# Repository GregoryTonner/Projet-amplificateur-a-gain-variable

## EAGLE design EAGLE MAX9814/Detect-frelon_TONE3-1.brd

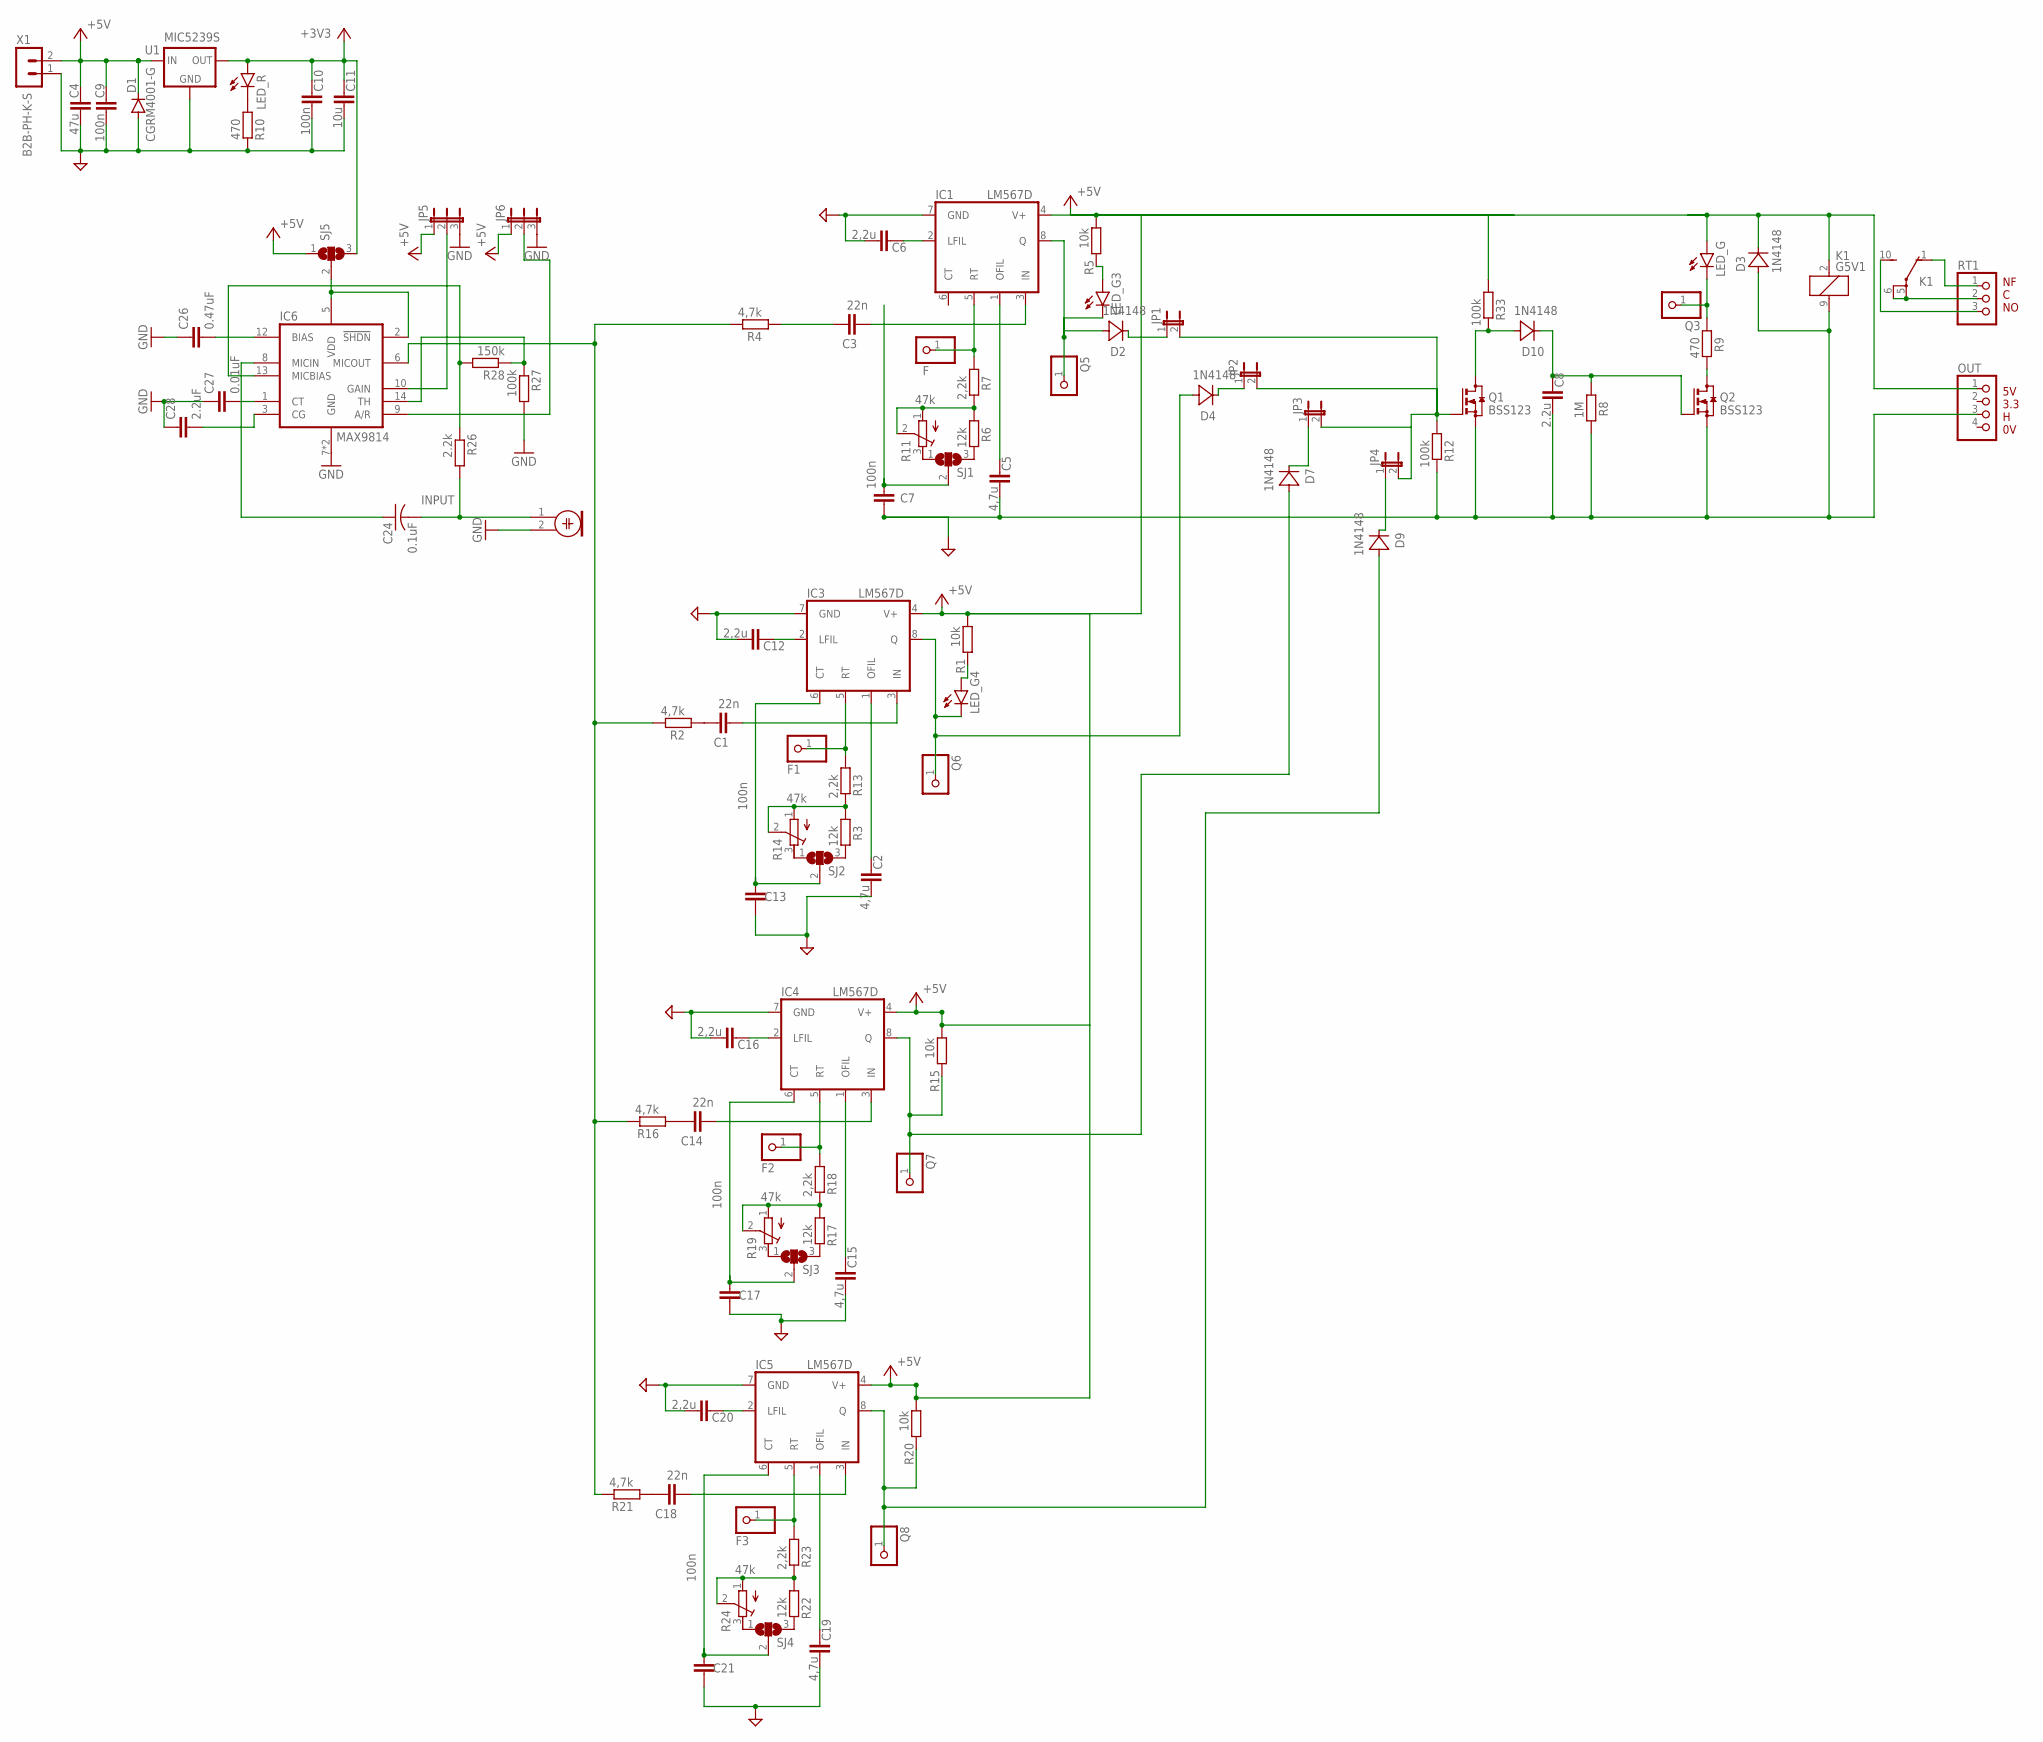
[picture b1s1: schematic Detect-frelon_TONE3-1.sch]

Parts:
C1, C3, C14, C18: 22n; C1206
C2, C5, C15, C19: 4,7u; C1206
C4: 47u; C1210
C6, C12, C16, C20: 2,2u; C1206
C7, C13, C17, C21: 100n; C1210
C8: 2.2u; C1210
C9, C10: 100n; C1206
C11: 10u; C1210
C24: 0.1uF; C0805K
C26: 0.47uF; C1206
C27: 0.01uF; C1206
C28: 2.2uF; C1206
D1: CGRM4001-G; SOD-123_MINI-SMA
D2, D3, D4, D7, D9, D10: 1N4148; VISHAY_1N4148W-E3-08_0
F, F1, F2, F3: PINHD-1X1; 1X01
IC1, IC3, IC4, IC5: LM567D; SO08
IC6: MAX9814; TDFN14-EP
JP1, JP2, JP3, JP4: JP1E; JP1
JP5, JP6: JP2E; JP2
K1: G5V1
LED_G, LED_G3, LED_G4: LEDSMT1206; 1206
LED_R: LEDSMT1206; 1206
M2: ELECTRET_MICROPHON-WM-62PC/62PK; WM-62PC/62PK
OUT: PINHD-1X4; 1X04
Q1, Q2: BSS123; SOT23
Q3, Q5, Q6, Q7, Q8: PINHD-1X1; 1X01
R1, R5, R15, R20: 10k; R1206
R2, R4, R16, R21: 4,7k; R1206
R3, R6, R17, R22: 12k; R1206
R7, R13, R18, R23: 2,2k; R1206
R8: 1M; R1206
R9, R10: 470; R1206
R11, R14, R19, R24: 47k; RTRIM3296W
R12, R27, R33: 100k; R1206
R26: 2.2k; R1206
R28: 150k; R1206
RT1: PINHD-1X3; 1X03
SJ1, SJ2, SJ3, SJ4, SJ5: SJ2W; SJ_2
U1: MIC5239S; SOT223
X1: B2B-PH-K-S

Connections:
+3V3: C10.1, C11.1, LED_R.A, SJ5.3, U1.3 (OUT)
+5V: C4.1, C9.1, D1.C, D3.1 (C), IC1.4 (V+), IC3.4 (V+), IC4.4 (V+), IC5.4 (V+), JP5.1, JP6.1, K1.2 (1), LED_G.A, OUT.1, R1.1, R5.1, R15.1, R20.1, R33.1, SJ5.1, U1.1 (IN), X1.2
GND: C2.2, C4.2, C5.2, C6.2, C7.2, C8.2, C9.2, C10.2, C11.2, C12.2, C13.2, C15.2, C16.2, C17.2, C19.2, C20.2, C21.2, C26.1, C27.1, C28.1, D1.A, D3.2 (A), IC1.7 (GND), IC3.7 (GND), IC4.7 (GND), IC5.7 (GND), IC6.7 (GND), IC6.EP (GND), JP5.3, JP6.3, K1.9 (2), M2.2, OUT.3, Q1.2 (S), Q2.2 (S), R8.2, R10.2, R12.2, R27.2, U1.2 (GND), U1.4 (GND), X1.1
INPUT: C24.2, M2.1, R26.2
unnamed: C3.1, R4.1
unnamed: F.1, IC1.5 (RT), R7.1
unnamed: IC6.10 (GAIN), JP5.2
unnamed: LED_R.C, R10.1
unnamed: C16.1, IC4.2 (LFIL)
unnamed: C8.1, D10.1 (C), Q2.1 (G), R8.1
unnamed: C12.1, IC3.2 (LFIL)
unnamed: C2.1, IC3.1 (OFIL)
unnamed: C6.1, IC1.2 (LFIL)
unnamed: C5.1, IC1.1 (OFIL)
unnamed: R6.2, SJ1.3
unnamed: Q2.3 (D), R9.2
unnamed: R6.1, R7.2, R11.1 (A), R11.2 (S)
unnamed: D2.1 (C), JP1.1
unnamed: LED_G.C, Q3.1, R9.1
unnamed: C1.1, R2.1
unnamed: K1.5, K1.6, RT1.2
unnamed: C13.1, IC3.6 (CT), SJ2.2
unnamed: R11.3 (E), SJ1.1
unnamed: C7.1, SJ1.2
unnamed: LED_G4.A, R1.2
unnamed: F1.1, IC3.5 (RT), R13.1
unnamed: R3.1, R13.2, R14.1 (A), R14.2 (S)
unnamed: C3.2, IC1.3 (IN)
unnamed: D2.2 (A), IC1.8 (Q), LED_G3.C, Q5.1
unnamed: R3.2, SJ2.3
unnamed: R14.3 (E), SJ2.1
unnamed: C1.2, IC3.3 (IN)
unnamed: D4.2 (A), IC3.8 (Q), LED_G4.C, Q6.1
unnamed: C15.1, IC4.1 (OFIL)
unnamed: C14.1, R16.1
unnamed: C17.1, IC4.6 (CT), SJ3.2
unnamed: F2.1, IC4.5 (RT), R18.1
unnamed: R17.1, R18.2, R19.1 (A), R19.2 (S)
unnamed: R17.2, SJ3.3
unnamed: R19.3 (E), SJ3.1
unnamed: C14.2, IC4.3 (IN)
unnamed: D7.2 (A), IC4.8 (Q), Q7.1, R15.2
unnamed: C27.2, IC6.1 (CT)
unnamed: C20.1, IC5.2 (LFIL)
unnamed: C19.1, IC5.1 (OFIL)
unnamed: C18.1, R21.1
unnamed: C21.1, IC5.6 (CT), SJ4.2
unnamed: F3.1, IC5.5 (RT), R23.1
unnamed: R22.1, R23.2, R24.1 (A), R24.2 (S)
unnamed: R22.2, SJ4.3
unnamed: R24.3 (E), SJ4.1
unnamed: C18.2, IC5.3 (IN)
unnamed: D9.2 (A), IC5.8 (Q), Q8.1, R20.2
unnamed: JP1.2, JP2.2, JP3.2, JP4.2, Q1.1 (G), R12.1
unnamed: C28.2, IC6.3 (CG)
unnamed: IC6.13 (MICBIAS), R26.1, R28.2
unnamed: C24.1, IC6.8 (MICIN)
unnamed: IC6.14 (TH), R27.1, R28.1
unnamed: C26.2, IC6.12 (BIAS)
unnamed: IC6.9 (A/R), JP6.2
unnamed: IC6.2 (!SHDN), IC6.5 (VDD), SJ5.2
unnamed: IC6.6 (MICOUT), R2.2, R4.2, R16.2, R21.2
unnamed: LED_G3.A, R5.2
unnamed: D10.2 (A), Q1.3 (D), R33.2
unnamed: D4.1 (C), JP2.1
unnamed: D7.1 (C), JP3.1
unnamed: D9.1 (C), JP4.1
NF: K1.1 (O), RT1.1
NO: K1.10 (S), RT1.3

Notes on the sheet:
5V 3.3 H 0V
NF C NO

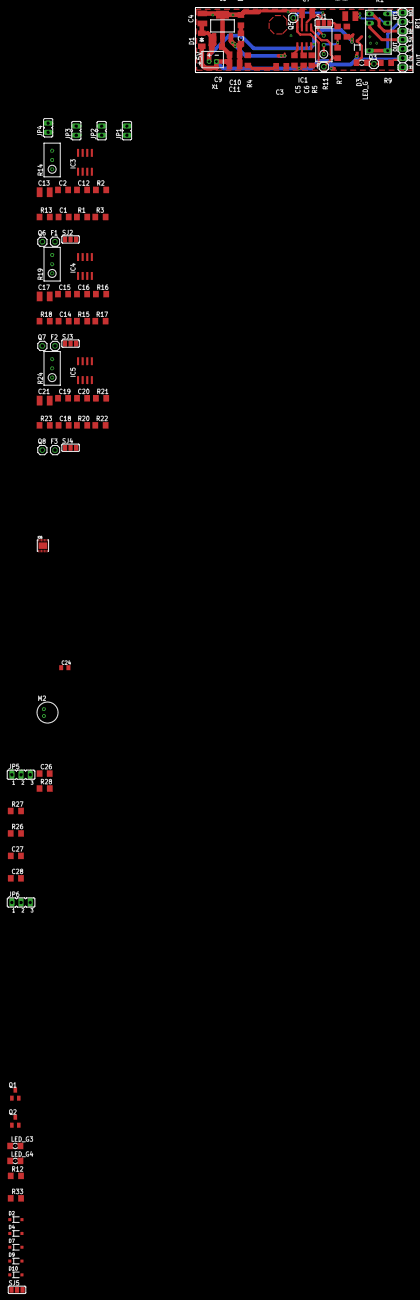
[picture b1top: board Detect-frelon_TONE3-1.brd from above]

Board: 2 copper layers, 60.0 x 17.9 mm, 97 parts (0 on the bottom side), 69 nets.

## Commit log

2022-02-03 Create Rapport de séance
2022-02-04 Update Rapport de séance

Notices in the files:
parts and their libraries:
micrel: Copyright (C) 2008, Bob Starr
